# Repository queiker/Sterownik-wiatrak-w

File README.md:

# Sterownik-wiatrak-w
sterownik waitraków w komputerze projekt w trakcie rozwoju
wymaga jeszcze wielu poprawek

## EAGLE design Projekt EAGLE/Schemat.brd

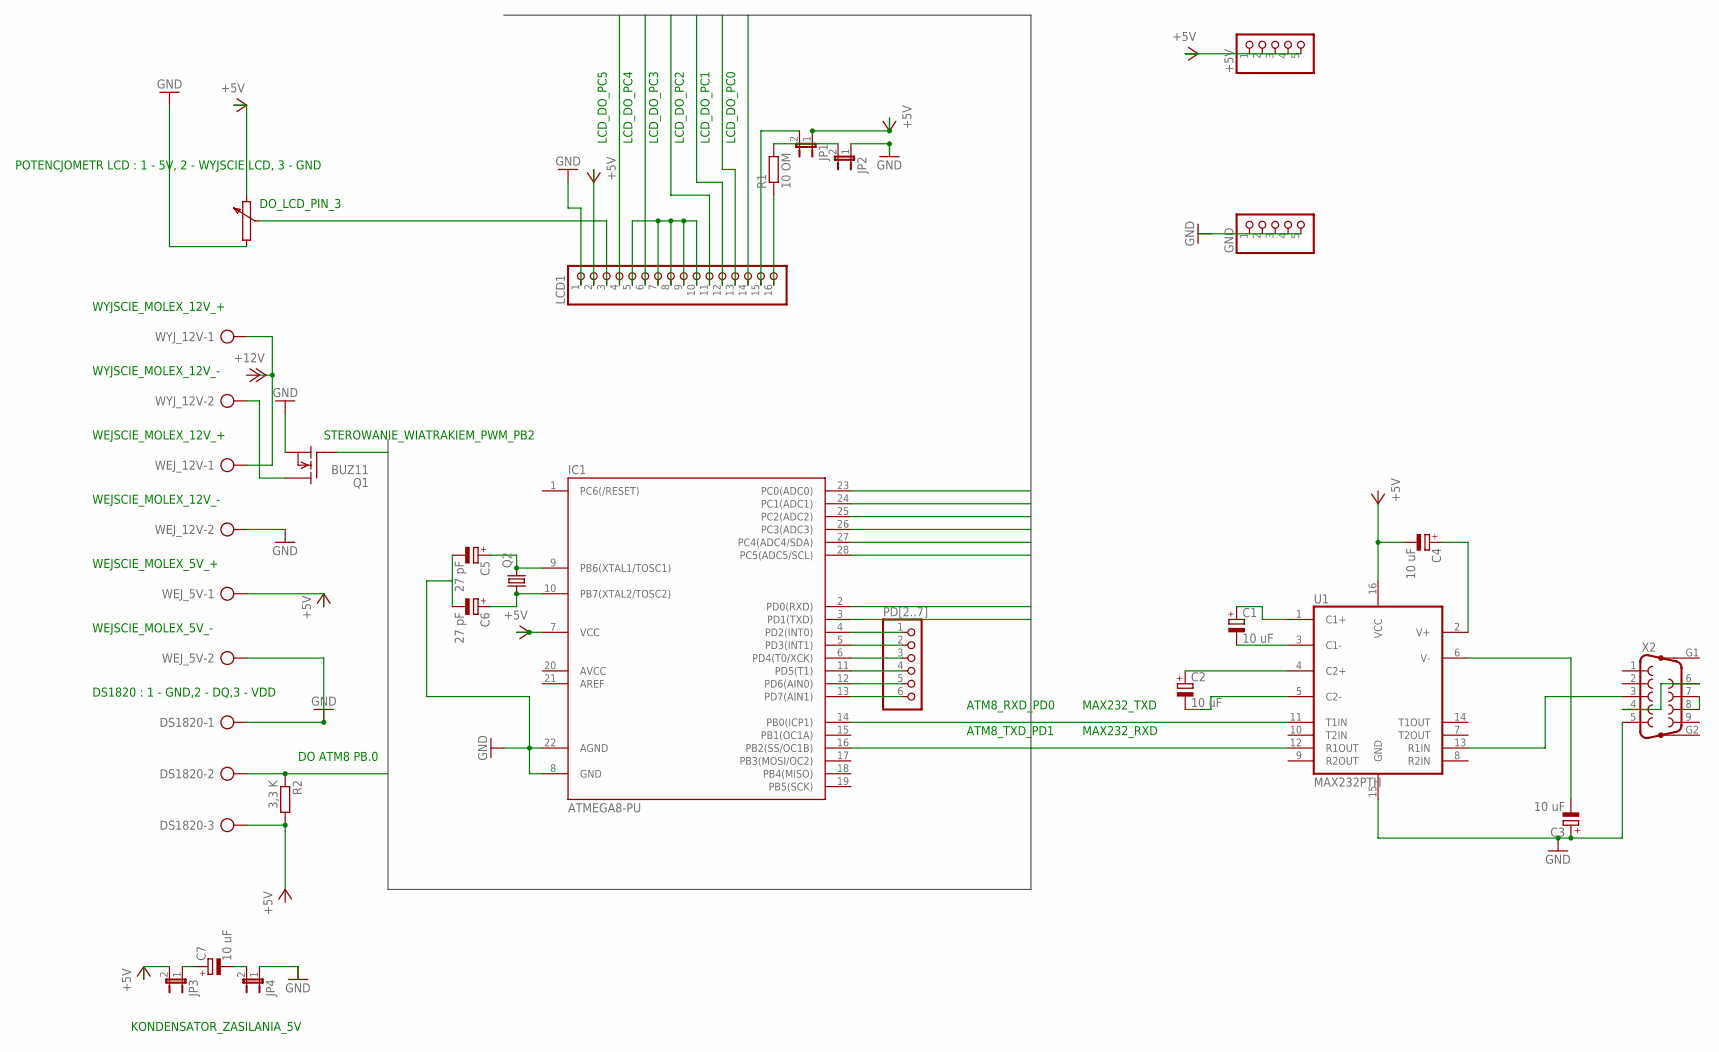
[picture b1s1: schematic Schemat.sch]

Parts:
+5V: PINHD-1X5; 1X05
C1, C2, C3, C4, C7: 10 uF; E5-10,5
C5, C6: 27 pF; E5-10,5
DS1820: AK500/3-H
GND: PINHD-1X5; 1X05
IC1: ATMEGA8-PU; DIL28-3
JP1, JP2, JP3, JP4: JP1E; JP1
LCD1: PINHD-1X16; 1X16
PD[2..7]: PINHD-1X6; 1X06
Q1: BUZ11; TO220
Q2: CRYSTALHC49S; HC49/S
R1: 10 OM; 0207/15
R2: 3,3 K; 0207/15
U1: MAX232PTH; DIL16
WEJ_5V, WEJ_12V: AK500/2-H
WYJ_12V: AK500/2-H
X2: F09HP

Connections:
+5V: +5V.1, +5V.2, +5V.3, +5V.4, +5V.5, IC1.7 (VCC), JP1.1, JP3.2, LCD1.2, WEJ_5V.1
GND: C3.+, C5.-, C6.-, DS1820.1, GND.1, GND.2, GND.3, GND.4, GND.5, IC1.8 (GND), IC1.22 (AGND), JP2.1, JP4.1, LCD1.1, Q1.3 (S), U1.15 (GND), WEJ_5V.2, WEJ_12V.2, X2.5
unnamed: C1.-, U1.3 (C1-)
unnamed: C1.+, U1.1 (C1+)
unnamed: C2.+, U1.4 (C2+)
unnamed: C2.-, U1.5 (C2-)
unnamed: X2.4, X2.6
unnamed: X2.7, X2.8
unnamed: U1.13 (R1IN), X2.3
unnamed: C4.-, U1.16 (VCC)
unnamed: C3.-, U1.6 (V-)
unnamed: C4.+, U1.2 (V+)
unnamed: C7.+, JP3.1
unnamed: C7.-, JP4.2
unnamed: IC1.4 (PD2(INT0)), PD[2..7].1
unnamed: IC1.5 (PD3(INT1)), PD[2..7].2
unnamed: DS1820.3, R2.2
unnamed: IC1.6 (PD4(T0/XCK)), PD[2..7].3
unnamed: WEJ_12V.1, WYJ_12V.1
unnamed: IC1.11 (PD5(T1)), PD[2..7].4
unnamed: Q1.2 (D), WYJ_12V.2
unnamed: LCD1.5, LCD1.7, LCD1.8, LCD1.9, LCD1.10
unnamed: IC1.12 (PD6(AIN0)), PD[2..7].5
unnamed: C5.+, IC1.9 (PB6(XTAL1/TOSC1)), Q2.2
unnamed: IC1.13 (PD7(AIN1)), PD[2..7].6
unnamed: JP1.2, LCD1.15
unnamed: JP2.2, R1.2
unnamed: C6.+, IC1.10 (PB7(XTAL2/TOSC2)), Q2.1
unnamed: LCD1.16, R1.1
PB0: DS1820.2, IC1.14 (PB0(ICP1)), R2.1
PB2: IC1.16 (PB2(SS/OC1B)), Q1.1 (G)
PC0: IC1.23 (PC0(ADC0)), LCD1.14
PC1: IC1.24 (PC1(ADC1)), LCD1.13
PC2: IC1.25 (PC2(ADC2)), LCD1.12
PC3: IC1.26 (PC3(ADC3)), LCD1.11
PC4: IC1.27 (PC4(ADC4/SDA)), LCD1.6
PC5: IC1.28 (PC5(ADC5/SCL)), LCD1.4
PD0: IC1.2 (PD0(RXD)), U1.11 (T1IN)
PD1: IC1.3 (PD1(TXD)), U1.12 (R1OUT)

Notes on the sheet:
MAX232_TXD
MAX232_RXD
WEJSCIE_MOLEX_12V_+
WEJSCIE_MOLEX_12V_-
WEJSCIE_MOLEX_5V_+
WEJSCIE_MOLEX_5V_-
DS1820 : 1 - GND,2 - DQ,3 - VDD
ATM8_RXD_PD0
ATM8_TXD_PD1
POTENCJOMETR LCD : 1 - 5V, 2 - WYJSCIE LCD, 3 - GND
DO ATM8 PB.0
WYJSCIE_MOLEX_12V_+
WYJSCIE_MOLEX_12V_-
STEROWANIE_WIATRAKIEM_PWM_PB2
DO_LCD_PIN_3
LCD_DO_PC5
LCD_DO_PC4
LCD_DO_PC3
LCD_DO_PC2
LCD_DO_PC1
LCD_DO_PC0
KONDENSATOR_ZASILANIA_5V

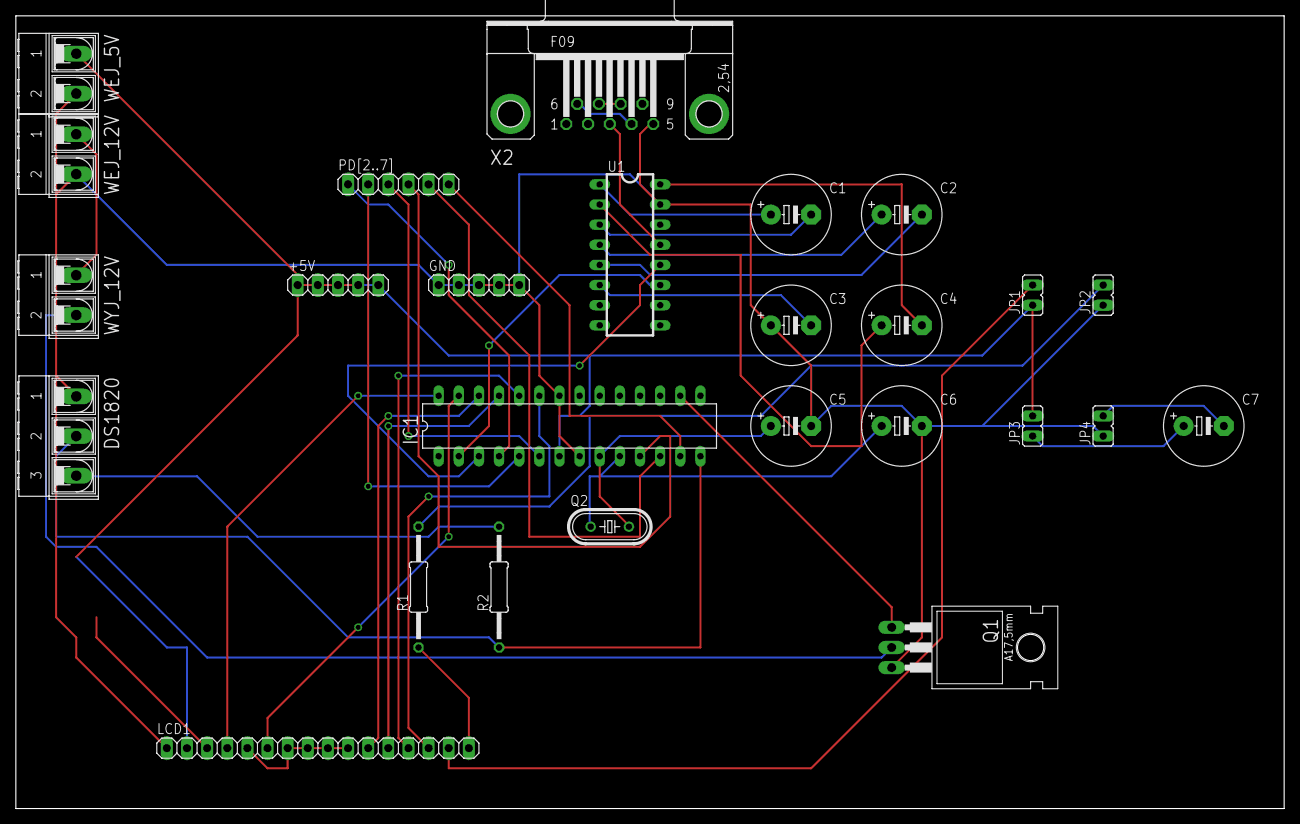
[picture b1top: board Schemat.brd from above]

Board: 2 copper layers, 160.0 x 100.0 mm, 26 parts (0 on the bottom side), 39 nets.

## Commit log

2020-10-21 zamiana złącza na potencjometr

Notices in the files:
parts and their libraries:
SparkFun: Licensing: CC v3.0 Share-Alike You are welcome to use this library for commercial purposes.
